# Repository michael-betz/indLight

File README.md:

# indLight
Controller for indirect room lighting using 12 V WS2811 LED strips. Based on the ESP8266-2.

Software will be comming soon (with MQTT client).

## Pictures

This is the panelized version which includes a top lid, to be mounted with stand-offs:

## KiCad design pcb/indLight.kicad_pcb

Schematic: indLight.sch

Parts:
C1, C2, C5, C9: 470n; C_0805_HandSoldering
C3, C11: 33u; Tantalum_Case-C_EIA-6032-28_Hand
C4, C7: 100n; C_0805_HandSoldering
C6, C8: 2u2; C_0805_HandSoldering
D1, D3, D4, D5: B5819WS; D_SOD-323_HandSoldering
D2: LED; LED_1206
L1: 22uH; DO1608
P1: TTL_232R_3V3; Pin_Header_Straight_1x06_Pitch2.54mm
P2: CONN_01X02; SW_PUSH_6mm
P3, P4: CONN_01X04; Socket_Strip_Straight_1x04
R1, R5, R6, R9: 10k; R_0805_HandSoldering
R2: 249R; R_0805_HandSoldering
R3: 750R; R_0805_HandSoldering
R4: 16.5k; R_0805_HandSoldering
R7: 1k; R_0805_HandSoldering
R8: 56R; R_0805_HandSoldering
U1: REG1117; SOT-223
U2: LT1933; SOT-23-6_Handsoldering
U3: SN74LVC2G17; SOT-23-6_Handsoldering
U4: esp8266_esp-02; ESP8266_ESP-02
W1, W2, W3, W4: TEST_1P; MountingHole_3.2mm_M3

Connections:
+3V3: C8.1, C9.1, C11.1, D4.2 (A), L1.1, R4.1, R5.1, R6.1, R8.2, R9.1, U4.4 (3V3), U4.5 (CH_PD)
+5V: C2.1, C5.1, P4.1, R2.2, U1.2 (OUT), U1.4 (OUT), U3.5 (VCC)
+12V: C1.1, C3.1, C6.1, D5.1 (K), P3.1, U1.3 (IN), U2.4, U2.5
/ESP_G2: R9.2, U3.3 (D), U4.7 (GPIO2)
/ESP_RX: R7.1, U3.1 (D), U4.2 (RX)
/ESP_TX: P1.5 (RXD_IN), U4.3 (TX)
GND: C1.2, C2.2, C3.2, C5.2, C6.2, C8.2, C9.2, C11.2, D1.2 (A), D2.1 (K), P1.1 (GND), P2.2, P3.3, P4.3, R1.1, R3.1, U2.2, U3.2 (GND), U4.1 (GND), W1.1, W2.1, W3.1, W4.1
unnamed: C4.1, D1.1 (K), L1.2, U2.6
unnamed: C4.2, D4.1 (K), U2.1
unnamed: C7.1, P2.1, R6.2, U4.8 (/RST)
unnamed: C7.2, D3.1 (K), P1.6 (RTS)
unnamed: D2.2 (A), R8.1
unnamed: D3.2 (A), R5.2, U4.6 (GPIO0)
unnamed: D5.2 (A), P1.3 (5V_USB)
unnamed: P1.4 (TXD), R7.2
unnamed: P3.2, U3.6 (O)
unnamed: P4.2, U3.4 (O)
unnamed: R1.2, R4.2, U2.3
unnamed: R2.1, R3.2, U1.1 (ADJ)

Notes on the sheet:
Reset button
RTS pulled low to flash
3.2 mm mounting holes
Alternative config. U1: LM317 R2: 200R R1: 590R

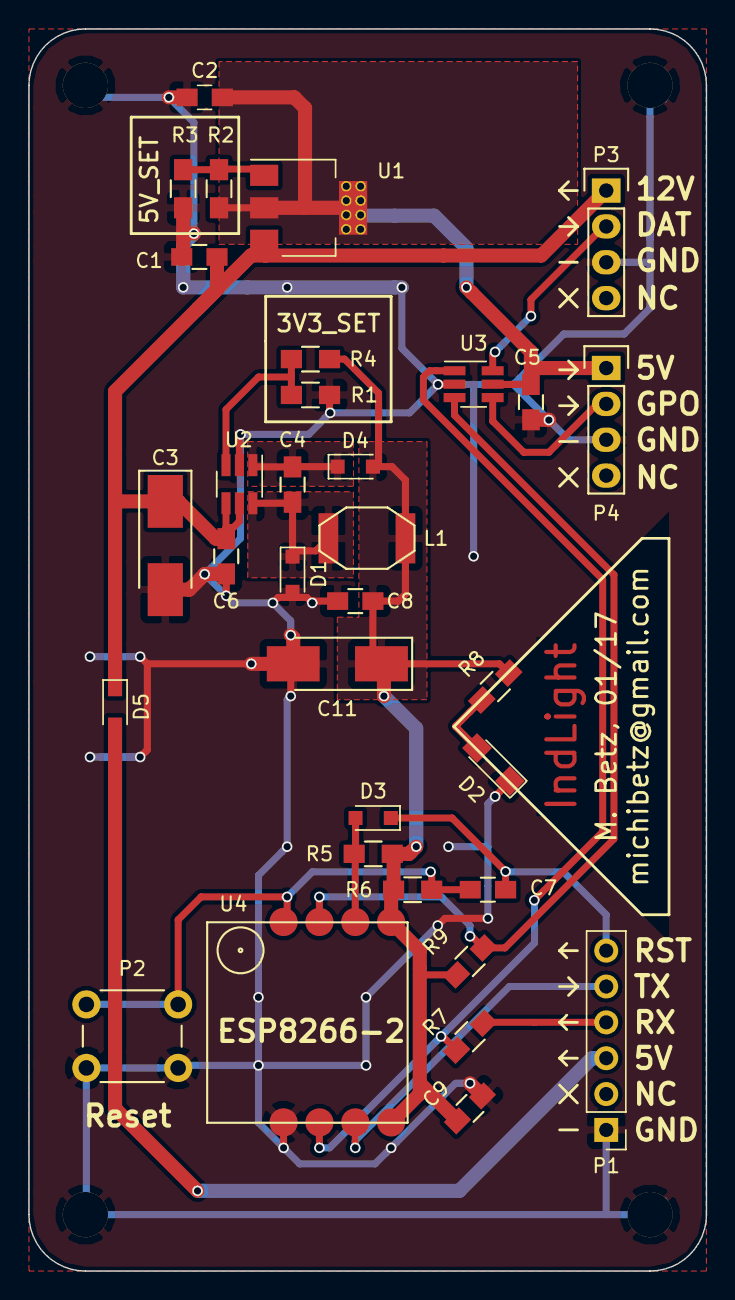
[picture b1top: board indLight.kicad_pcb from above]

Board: 2 copper layers, 48.0 x 88.0 mm, 37 parts (0 on the bottom side), 19 nets.

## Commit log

2017-01-10 Initial
2017-01-10 Changed image size
2017-01-16 REV1. Added top lid, better DCDC, gerb. Ordered
2019-12-26 organized files in pcb dir
2019-12-26 add player code
2019-12-29 add perlin noise animation
2020-03-15 indLight.c: Set color order to RGB
2020-03-15 add platformIO based esp8266 firmware
2020-03-15 pw.h: external wifi passwords
2020-03-15 clip UDP to actual number of LEDs
2020-03-15 add note about protocol
2020-03-15 shorter
2020-03-15 Further cleanup, tested on hardware
2020-03-15 remove CI
2020-03-15 comments
2020-03-15 main.ino: remove CURRENT_TIME due to full re-build every time
2020-03-15 actually remove CURRENT_TIME
2020-05-02 fix led strip type for wall
2020-10-18 add log file to daemon
